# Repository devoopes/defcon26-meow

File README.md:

# DEFCON 26 - Maneki-neko Badge

photo by [Roberto Baldwin](https://twitter.com/@strngwys)  

Follow the Twitter for updates [@ManekiNekoDC](https://twitter.com/ManekiNekoDC)  

We went to DEF CON 26 and launched an unofficial DEF CON badge. We wanted to be able to create something different and unique to some of the other designs out there. The badge is controlled by an STM32 that drives the servo and dual 16 segment LEDS on the front. We attached a 3d printed arm to the servo. All the files are source code are Open Source and in this repo. You are welcome to make one yourself via OSHpark or JLC PCB. Gerber files are located in the repo.  

### Art Design:
Our art was done by Jeff Chang.
http://www.jeffchangart.com/  
Twitter [@jeffchangart](https://twitter.com/jeffchangart)  
Instagram [@jeffchangart](https://instagram.com/jeffchangart)  

All the drafts, and formats of the art can be found in the /art/ directory.

Lanyards were done by https://customlanyards4all.com

### Meowtronics

First done with KiCAD but abandoned after more experienced help was provided. <3 \
You can find all the Eagle files in the [eagle directory](https://github.com/SeanLeftBelow/defcon26-meow/tree/master/pcb/eagle).

Board is on [OSHpark](https://oshpark.com/shared_projects/X3Hxcson)

Guide is [here](https://github.com/SeanLeftBelow/defcon26-meow/tree/master/guide)

First look at the boards from the fab house.  

### SAO (Special Addons/ Shitty Addons)

Overall design is a copy of the main badge. See writeup [here](https://github.com/SeanLeftBelow/defcon26-meow/tree/master/addon)

### In The Mews

[Engadget: This cute Def Con badge beckons you to hack  it](https://www.engadget.com/2018/08/15/this-cute-def-con-badge-beckons-you-to-hack-it/  ) \
[Hackaday: ALL THE BADGES OF DEF CON 26 (VOL 1)](https://hackaday.com/2018/08/14/all-the-badges-of-def-con-26-vol-1/) \
[BadgeLife - A Hackaday Documentary](https://www.youtube.com/watch?v=G2fHKRONc6U) \

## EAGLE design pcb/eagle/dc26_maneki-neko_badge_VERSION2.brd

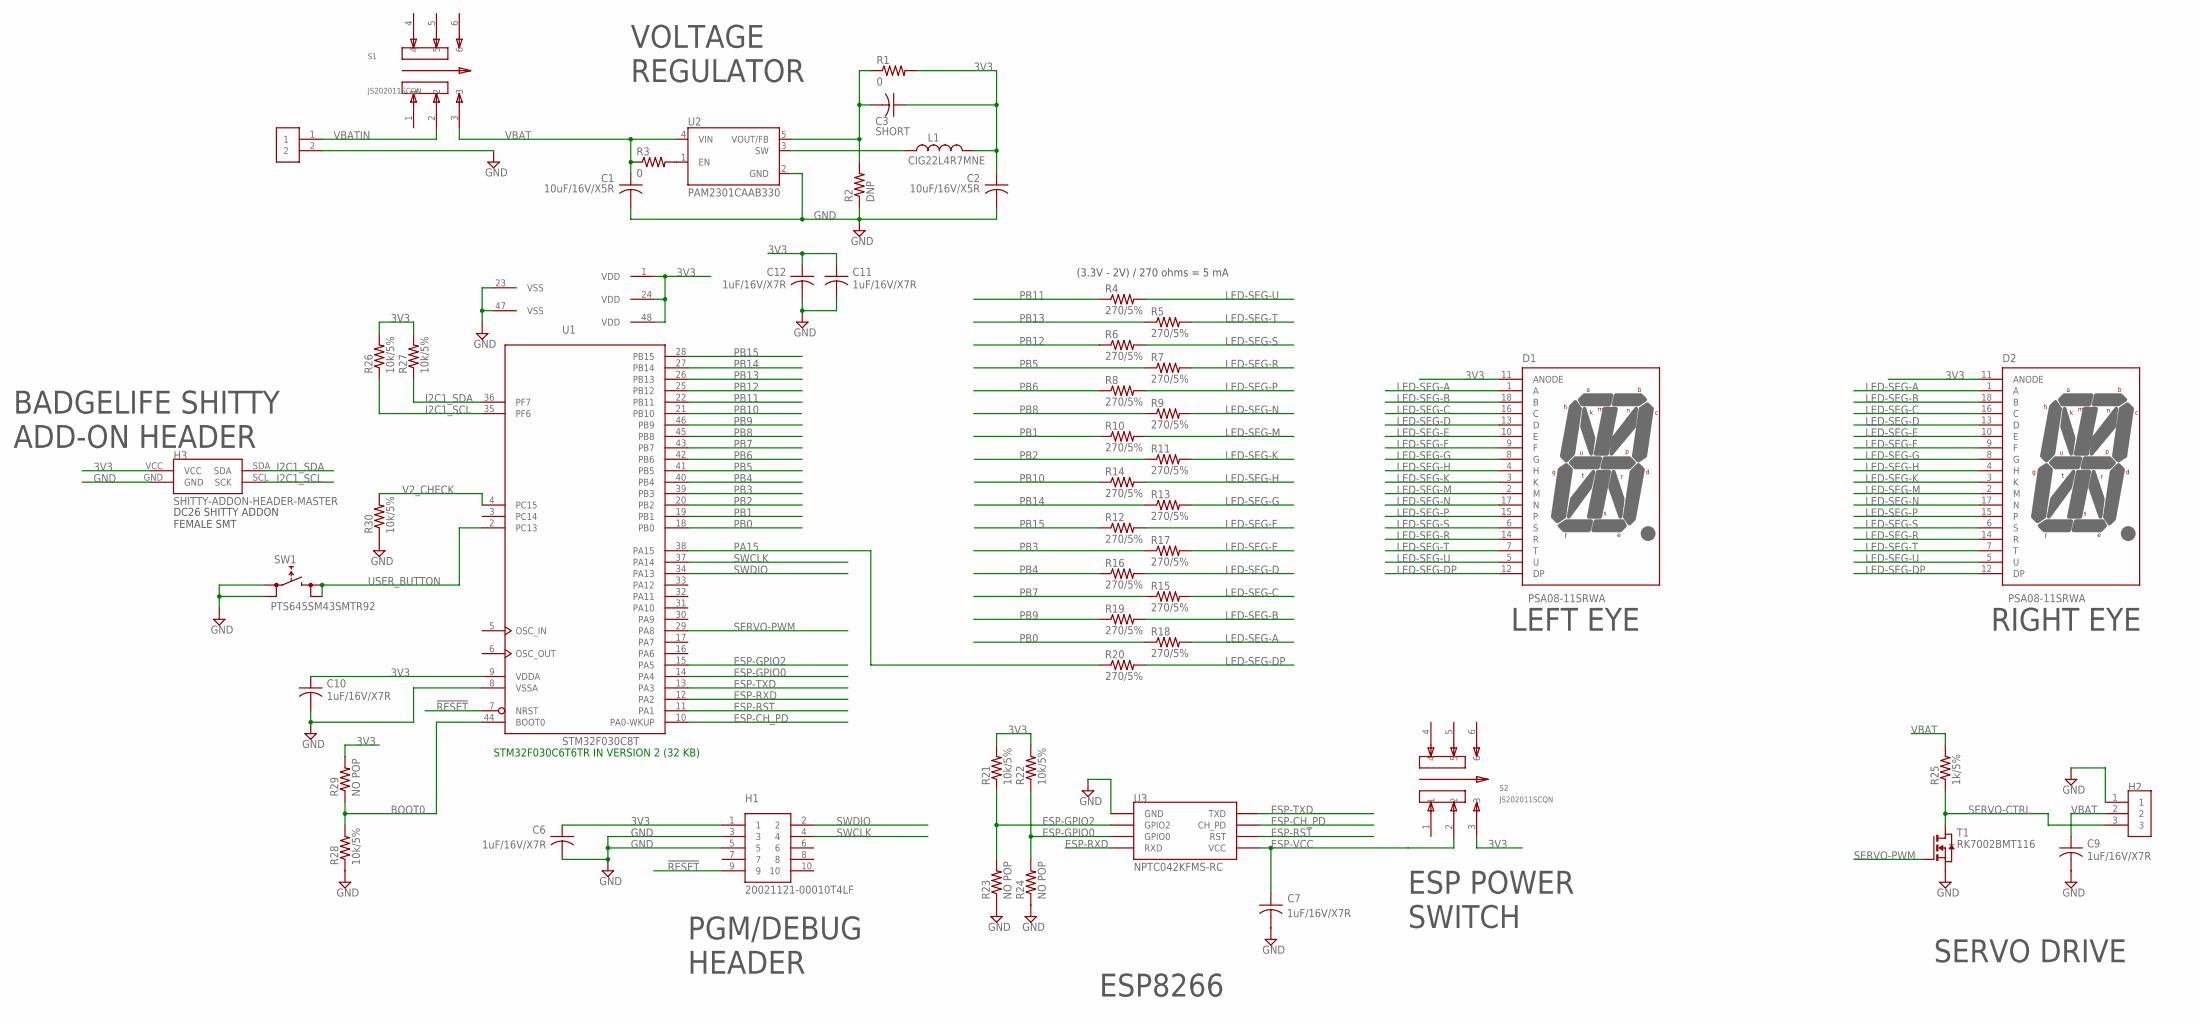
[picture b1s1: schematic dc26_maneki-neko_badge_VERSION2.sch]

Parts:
C1, C2: 10uF/16V/X5R; C0805
C3: SHORT; C0805
C6, C7, C9, C10, C11, C12: 1uF/16V/X7R; C0805
D1, D2: PSA08-11SRWA
H1: 20021121-00010T4LF
H2: M20-8890345R
H3: SHITTY-ADDON-HEADER-MASTER; 2X2-0.1INCH-FEMALE-SMT
H4: BATTPADS-SMT
L1: CIG22L4R7MNE; L-1008-US
R1, R3: 0; R0805
R2: DNP; R0805
R4, R5, R6, R7, R8, R9, R10, R11, R12, R13, R14, R15, R16, R17, R18, R19, R20: 270/5%; R0805
R21, R22, R26, R27, R28, R30: 10k/5%; R0805
R23, R24, R29: NO POP; R0805
R25: 1k/5%; R0805
S1, S2: JS202011SCQN; SW_JS202011SCQN
SW1: PTS645SM43SMTR92
T1: RK7002BMT116; SOT-23
U1: STM32F030C8T; LQFP48
U2: PAM2301CAAB330; SOT95P280X100-5N
U3: NPTC042KFMS-RC

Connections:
3V3: C2.1, C3.1, C6.1, C10.1, C11.1, C12.1, D1.11 (ANODE), D2.11 (ANODE), H1.1, H3.VCC, L1.P$2 (2), R1.2, R21.2, R22.2, R26.2, R27.2, R29.2, S2.3, U1.1 (VDD), U1.9 (VDDA), U1.24 (VDD), U1.48 (VDD)
!RESET: H1.9, U1.7 (NRST)
BOOT0: R28.2, R29.1, U1.44 (BOOT0)
ESP-CH_PD: U1.10 (PA0-WKUP), U3.3 (CH_PD)
ESP-GPIO0: R22.1, R24.2, U1.14 (PA4), U3.6 (GPIO0)
ESP-GPIO2: R21.1, R23.2, U1.15 (PA5), U3.4 (GPIO2)
ESP-RST: U1.11 (PA1), U3.5 (RST)
ESP-RXD: U1.12 (PA2), U3.8 (RXD)
ESP-TXD: U1.13 (PA3), U3.1 (TXD)
ESP-VCC: C7.1, S2.2, U3.7 (VCC)
GND: C1.2, C2.2, C6.2, C7.2, C9.2, C10.2, C11.2, C12.2, H1.3, H1.5, H2.1, H3.GND, H4.2, R2.1, R23.1, R24.1, R28.1, R30.1, SW1.1 (0), SW1.2 (0), T1.2 (S), U1.8 (VSSA), U1.23 (VSS), U1.47 (VSS), U2.2 (GND), U3.2 (GND)
I2C1_SCL: H3.SCL (SCK), R26.1, U1.35 (PF6)
I2C1_SDA: H3.SDA, R27.1, U1.36 (PF7)
LED-SEG-A: D1.1 (A), D2.1 (A), R18.2
LED-SEG-B: D1.18 (B), D2.18 (B), R19.2
LED-SEG-C: D1.16 (C), D2.16 (C), R15.2
LED-SEG-D: D1.13 (D), D2.13 (D), R16.2
LED-SEG-DP: D1.12 (DP), D2.12 (DP), R20.2
LED-SEG-E: D1.10 (E), D2.10 (E), R17.2
LED-SEG-F: D1.9 (F), D2.9 (F), R12.2
LED-SEG-G: D1.8 (G), D2.8 (G), R13.2
LED-SEG-H: D1.4 (H), D2.4 (H), R14.2
LED-SEG-K: D1.3 (K), D2.3 (K), R11.2
LED-SEG-M: D1.2 (M), D2.2 (M), R10.2
LED-SEG-N: D1.17 (N), D2.17 (N), R9.2
LED-SEG-P: D1.15, D2.15, R8.2
LED-SEG-R: D1.14 (R), D2.14 (R), R7.2
LED-SEG-S: D1.6 (S), D2.6 (S), R6.2
LED-SEG-T: D1.7 (T), D2.7 (T), R5.2
LED-SEG-U: D1.5 (U), D2.5 (U), R4.2
unnamed: L1.P$1 (1), U2.3 (SW)
unnamed: R3.2, U2.1 (EN)
unnamed: C3.2, R1.1, R2.2, U2.5 (VOUT/FB)
PA15: R20.1, U1.38 (PA15)
PB0: R18.1, U1.18 (PB0)
PB1: R10.1, U1.19 (PB1)
PB2: R11.1, U1.20 (PB2)
PB3: R17.1, U1.39 (PB3)
PB4: R16.1, U1.40 (PB4)
PB5: R7.1, U1.41 (PB5)
PB6: R8.1, U1.42 (PB6)
PB7: R15.1, U1.43 (PB7)
PB8: R9.1, U1.45 (PB8)
PB9: R19.1, U1.46 (PB9)
PB10: R14.1, U1.21 (PB10)
PB11: R4.1, U1.22 (PB11)
PB12: R6.1, U1.25 (PB12)
PB13: R5.1, U1.26 (PB13)
PB14: R13.1, U1.27 (PB14)
PB15: R12.1, U1.28 (PB15)
SERVO-CTRL: H2.3, R25.1, T1.1 (D)
SERVO-PWM: T1.3 (G), U1.29 (PA8)
SWCLK: H1.4, U1.37 (PA14)
SWDIO: H1.2, U1.34 (PA13)
USER_BUTTON: SW1.3 (1), SW1.4 (1), U1.2 (PC13)
V2_CHECK: R30.2, U1.4 (PC15)
VBAT: C1.1, C9.1, H2.2, R3.1, R25.2, S1.3, U2.4 (VIN)
VBATIN: H4.1, S1.2

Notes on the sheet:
RIGHT EYE
LEFT EYE
(3.3V - 2V) / 270 ohms = 5 mA
SERVO DRIVE
ESP8266
ESP POWER SWITCH
PGM/DEBUG HEADER
BADGELIFE SHITTY ADD-ON HEADER
VOLTAGE REGULATOR
STM32F030C6T6TR IN VERSION 2 (32 KB)

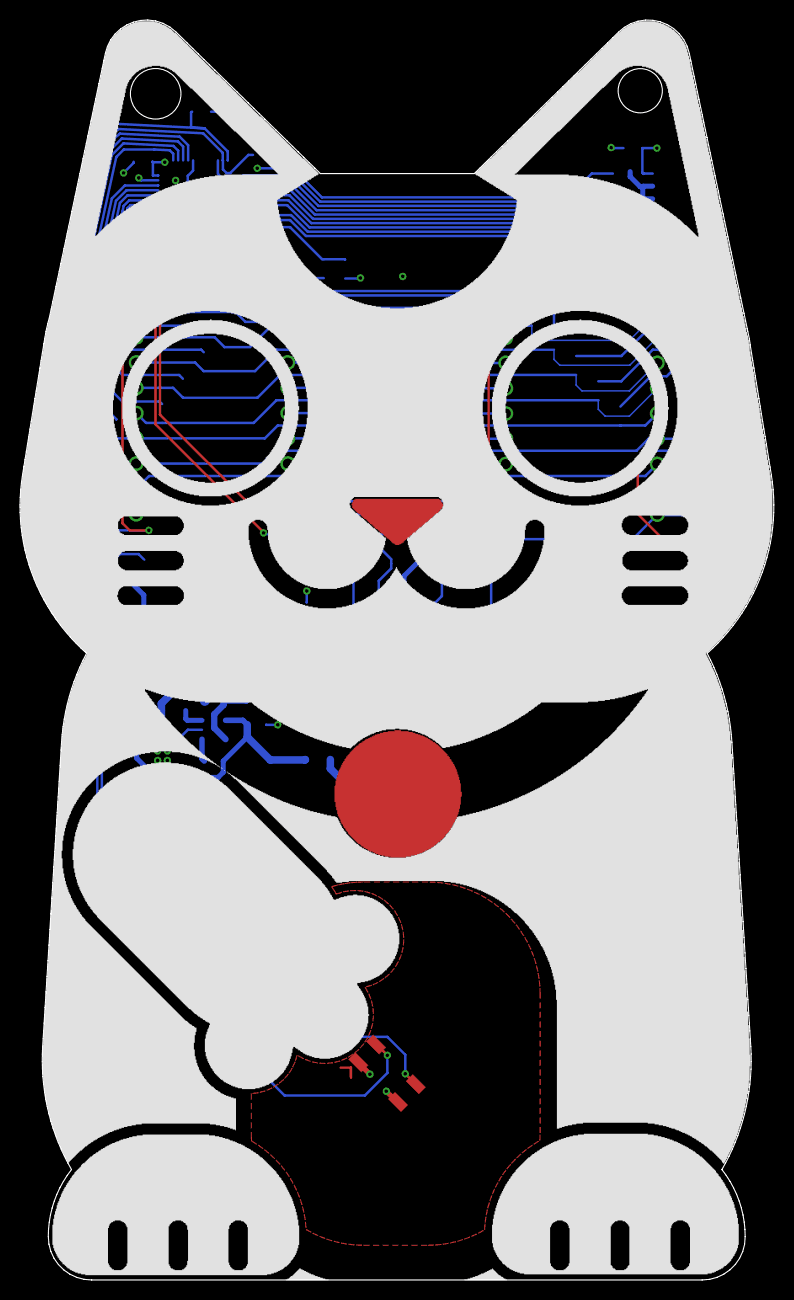
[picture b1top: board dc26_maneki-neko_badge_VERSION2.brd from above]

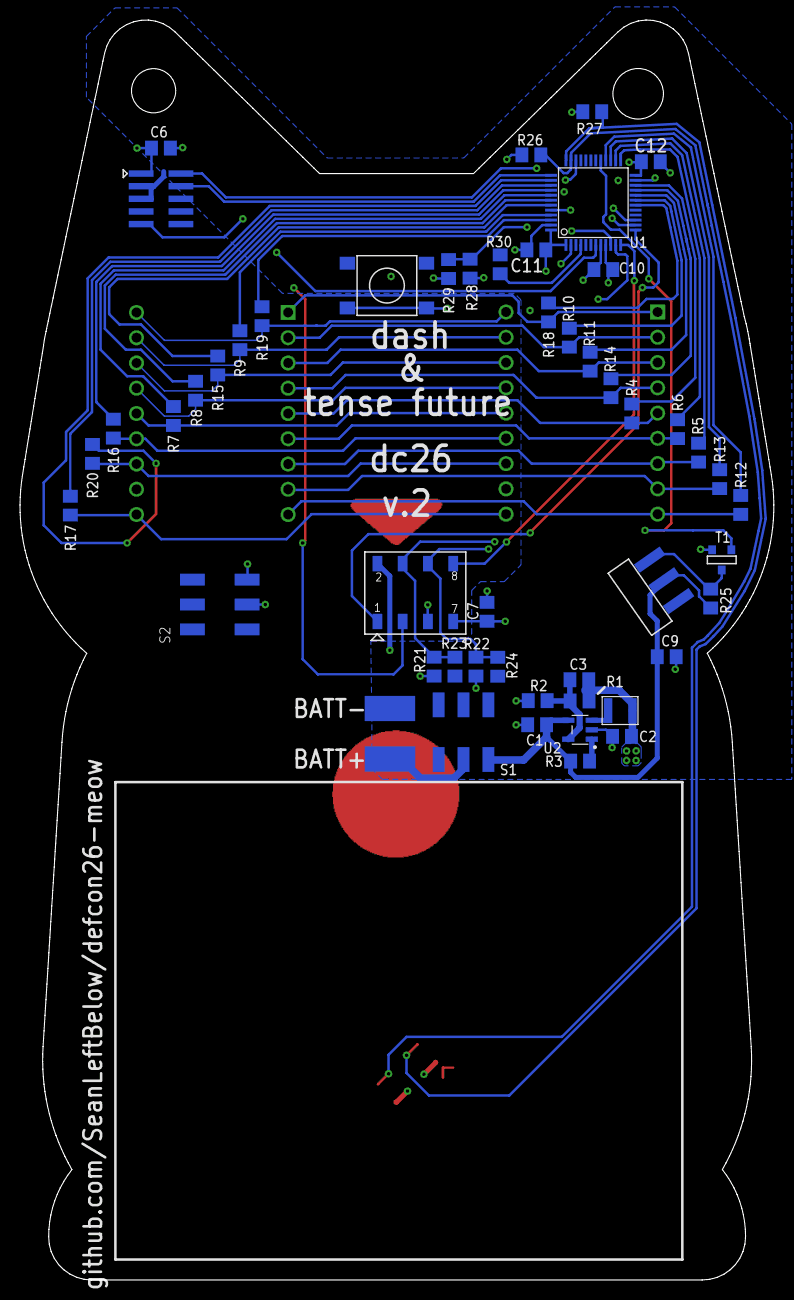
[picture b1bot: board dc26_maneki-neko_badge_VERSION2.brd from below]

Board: 4 copper layers, 75.8 x 126.7 mm, 53 parts (50 on the bottom side), 58 nets.

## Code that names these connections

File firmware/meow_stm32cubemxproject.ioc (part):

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Mcu.Name=STM32F030C8Tx
Mcu.Package=LQFP48
Mcu.UserName=STM32F030C8Tx
PA0.Signal=GPIO_Output
PA1.Signal=GPIO_Output
PA10.Signal=GPIO_Input
PA11.Signal=GPIO_Input
PA12.Signal=GPIO_Input
PA13.Mode=Serial_Wire
PA13.Signal=SYS_SWDIO
PA14.Mode=Serial_Wire
PA14.Signal=SYS_SWCLK
PA15.Signal=GPIO_Output
PA2.Signal=USART2_TX
PA3.Signal=USART2_RX
PA4.Signal=GPIO_Input
PA5.Signal=GPIO_Output
PA6.Signal=GPIO_Output
PA7.Signal=GPIO_Output
PA8.Signal=S_TIM1_CH1
PA9.Signal=GPIO_Output
PB0.Signal=GPIO_Output
PB1.Signal=GPIO_Output
PB10.Signal=GPIO_Output
PB11.Signal=GPIO_Output
PB12.Signal=GPIO_Output
PB13.Signal=GPIO_Output
PB14.Signal=GPIO_Output
PB15.Signal=GPIO_Output
PB2.Signal=GPIO_Output
PB3.Signal=GPIO_Output
PB4.Signal=GPIO_Output
PB5.Signal=GPIO_Output
PB6.Signal=GPIO_Output
PB7.Signal=GPIO_Output
PB8.Signal=GPIO_Output
PB9.Signal=GPIO_Output
PC13.Signal=GPIO_Input
PF6.Mode=I2C
PF6.Signal=I2C2_SCL
PF7.Mode=I2C
PF7.Signal=I2C2_SDA
RCC.SYSCLKFreq_VALUE=48000000
RCC.SYSCLKSource=RCC_SYSCLKSOURCE_PLLCLK
board=custom

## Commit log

2018-03-23 First art asset
2018-03-23 rotated
2018-05-25 meow.svg v1
    Adding first pass of meow SVG
2018-05-25 Finished base of v1
    Its aweful
2018-05-25 Trying some other samples
2018-05-25 Ok, im starting to be happy with this.
2018-05-25 adding osh
2018-05-25 Some older stuff
2018-05-25 Updates to move computers.
2018-05-25 Typo
2018-06-04 Adding Art and kiCAD
2018-06-09 initial commit of eagle files, schematics 95%
2018-06-09 adding eagle local backup files to .gitignore
2018-06-09 adding libraries i built or found, not part of stock eagle install
2018-06-10 board outline in, some minor edits to schematic, board ready for component placement
2018-06-11 some component placement, eyes locked in
2018-06-13 more layout. changed out connectors to support a clean 'art' (top) side. shooting for 2 layers, might need to be 4 to avoid a ton of routing time.
2018-06-14 completely regretting my decision to use eagle
2018-06-14 mini commit before taking a shower and letting autorouter mess around
2018-06-15 re-orging traces to eyes for clean routing, done routing left eye
2018-06-17 all led and high(er) speed signals routed... phewf
2018-06-18 pcb traces routed, just need to finish off GND and 3V3 rails
2018-06-20 finished routing incl 3v3 and gnd, except shitty addon connector (will route after artwork is added
2018-06-23 update gitignore, add intermediate art files, update layout file
2018-06-24 added copper art (nose, collar tag, and coin). just need to route shitty addon connector and i think its done
2018-06-25 silk fixed, drc errors fixed, going to export and send thru freedfm
2018-06-26 updated design (smt servo connector), out to freedfm, quote from seeed
2018-06-27 adjusted ref des line thickness, created fab/assy pkg for vendor RFQs. this might be the final form....
2018-06-27 added power switch and user button
2018-06-29 OUT TO FAB OMG 2560256025602560
2018-07-06 Cleanup
2018-07-11 adding in-progress for mini-meow add-on
2018-07-11 removed DS_Store
2018-07-12 added ground
2018-07-13 added net list, updated schematic, layout
2018-07-14 moved back from 2 resistors to 1
2018-07-19 updated kicad for new layout
2018-07-22 blank new project for stm32f030_8 (we are using c8t6)
2018-07-22 typo in .gitignore, Object/ => Objects/
2018-07-22 exported from illustrator
2018-07-23 Adding files for kicad import ease
2018-07-23 Made into 1 object
2018-07-24 Adding README back and some photos
2018-07-24 Updating
2018-07-25 pcb update, added working art files
2018-07-25 added -bak to gitignore
2018-07-25 updated library, added copper images
2018-07-25 BOM stuff
2018-07-25 updated pcb, maybe first final draft
2018-07-26 updated copper layers. added ground
2018-07-26 updated copper layers....again...
2018-07-26 updated some silkscreen text
2018-07-26 updated mask for copper
2018-07-26 Adding non gray version
2018-07-27 added gerber files
2018-07-27 Blender Files
2018-07-27 1.5 test
2018-07-27 Updating osh rev
2018-07-27 Cleanup and adding v2
2018-07-28 ignore updates, blank firmware template update, pcb paw fix (coin cutout for paw)
2018-07-28 led test implemented in firmware. dunno why the whitesilk svg changed but committing anyway.
2018-07-31 deleting files, will replace with new. accidentally been working from a different diretory.
2018-07-31 cubemx project generator included all kinds of unnecessary library files but im too lazy to work through them and write instructions on how to install dependencies so just deal with it.
2018-07-31 interrupt working, trying to make it trigger waving animation, but interrupt handler doesnt like calling user functions 2 deep for some reason (or something else im not catching)
2018-08-01 timed blink and paw wave animation, kind of interrupt based
2018-08-01 MVP candidate 1. commit all the things i dont care apparently i dont know how gitignore works whatever
2018-08-02 Arm (#3)
    * Blender Files
    * 1.5 test
    * Cleanup and adding v2
2018-08-02 BOM stuff (#4)
2018-08-02 Adding 3d files
2018-08-07 60 seconds and servo fix.
2018-08-11 update oshpark link
2018-08-15 Adding Twitter to README
2018-08-15 Fixing formating and adding more info
2018-08-15 update oshpark link (#5)
2018-08-16 commit cost reduction study text doc pt 1, moar updates tmrw
2018-08-18 created SAO Rev2 with correct connector orientation
2018-08-18 updated kicad to display layers and fix silk rotation
2018-08-18 Cleanup and README update
2018-08-18 Formatting issue
2018-08-18 More pictures
2018-08-18 Art (#6)
    * created SAO Rev2 with correct connector orientation
    * updated kicad to display layers and fix silk rotation
2018-08-18 rearranged art directory
2018-08-18 le formating sigh
2018-08-18 Lanyard stuff
2018-08-20 wrong image
2018-08-20 Delete lanyards.jpg
    Not updating.
2018-08-20 Fixing lanyard image
2018-09-05 version 2 start, cost reduction edits to schematic
2018-09-17 pcb v2 routed, bom edited, gerbers rendered - quote out to pcba house and dfm check to freedfm
2018-10-21 First rev of the guide
2018-10-21 jpg --> JPG
2018-10-21 width resize
2018-10-23 Wrap up for the guide
2018-10-23 Final typo check
2018-10-23 Final touches
2018-10-23 Werid md format thing
2018-10-23 Final draft
2018-10-23 Create LICENSE
2018-10-28 revised gerbers
2018-10-29 revised gerbers (#8)
